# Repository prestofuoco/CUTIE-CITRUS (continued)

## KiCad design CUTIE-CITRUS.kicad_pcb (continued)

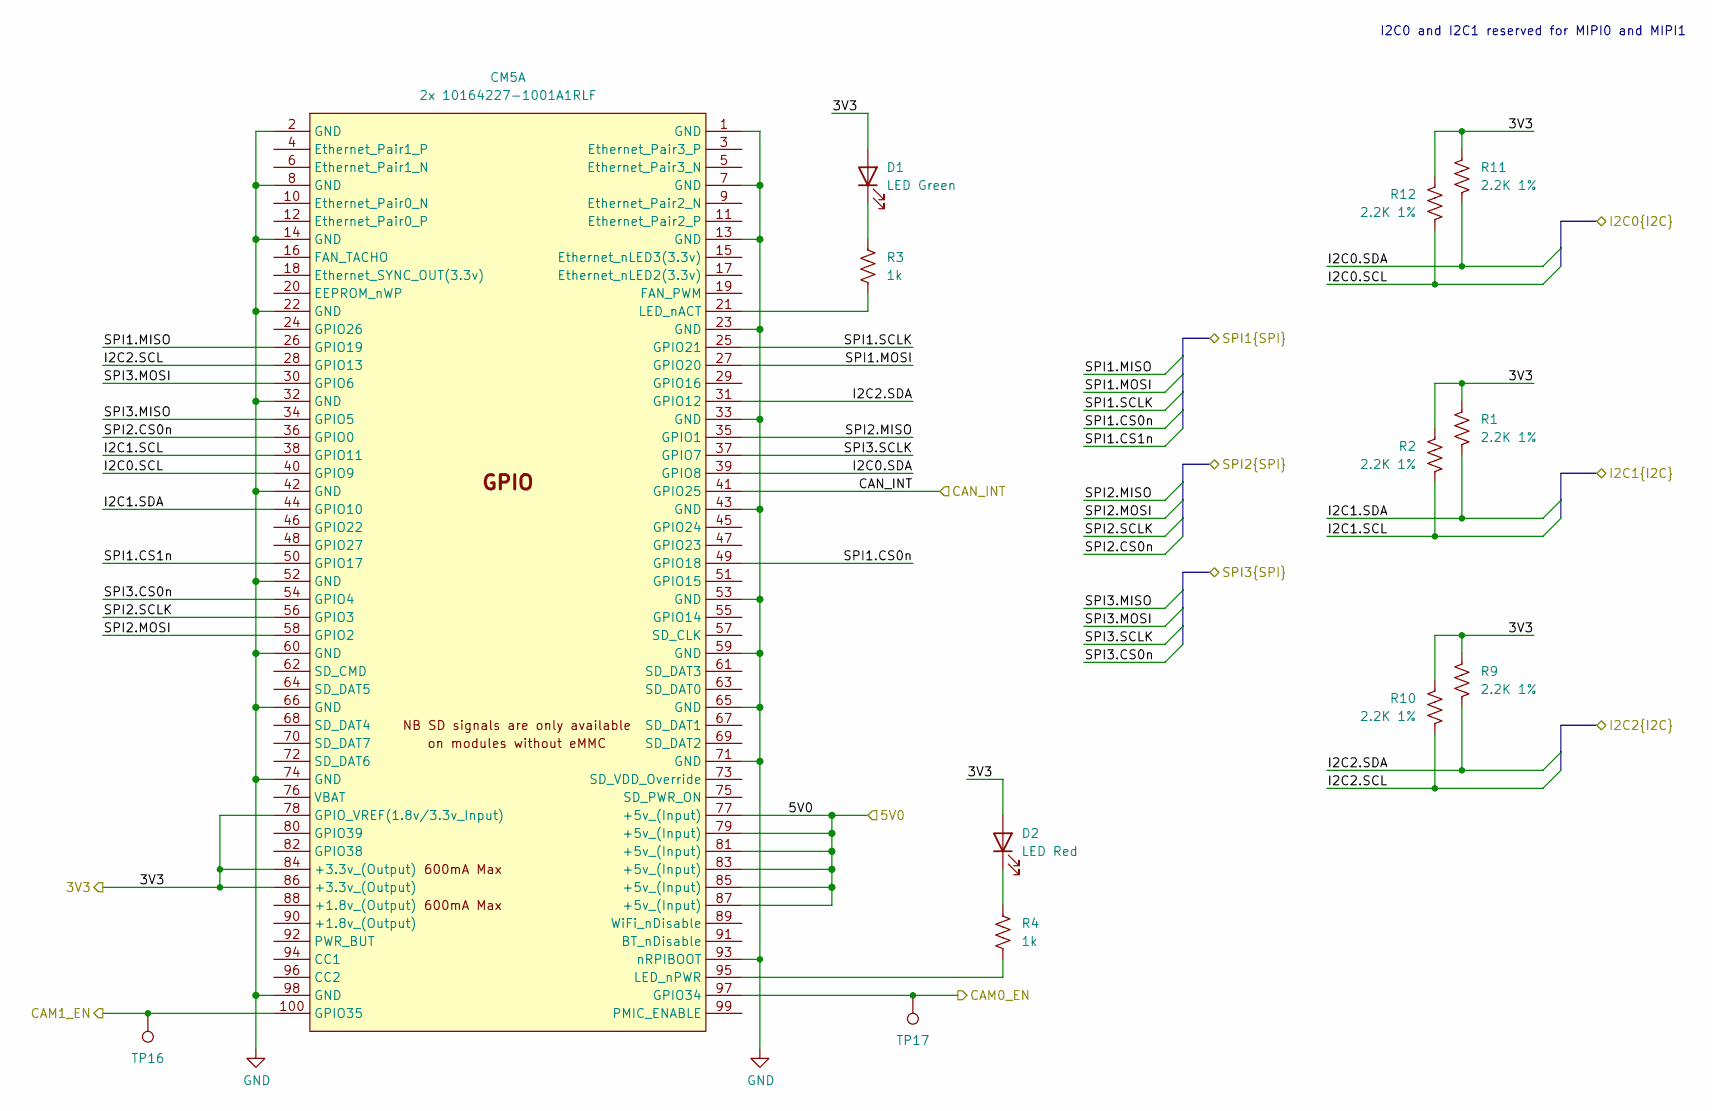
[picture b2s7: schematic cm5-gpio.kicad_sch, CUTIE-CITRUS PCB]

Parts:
CM5: 2x 10164227-1001A1RLF; RPi-CM5
D1: LED Green; LED_0603_1608Metric
D2: LED Red; LED_0603_1608Metric
R1, R2, R9, R10, R11, R12: 2.2K 1%; R_0402_1005Metric
R3, R4: 1k; R_0402_1005Metric
TP16, TP17: TestPoint; TestPoint_Pad_D1.0mm

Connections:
/Backplane Connector/5V0: CM5.77 (+5v_(Input)), CM5.79 (+5v_(Input)), CM5.81 (+5v_(Input)), CM5.83 (+5v_(Input)), CM5.85 (+5v_(Input)), CM5.87 (+5v_(Input)); also elsewhere on the board
/Backplane Connector/SPI2.CS0n: CM5.36 (GPIO0); also elsewhere on the board
/Backplane Connector/SPI2.MISO: CM5.35 (GPIO1); also elsewhere on the board
/Backplane Connector/SPI2.MOSI: CM5.58 (GPIO2); also elsewhere on the board
/Backplane Connector/SPI2.SCLK: CM5.56 (GPIO3); also elsewhere on the board
/CM5/3V3: CM5.78 (GPIO_VREF(1.8v/3.3v_Input)), CM5.84 (+3.3v_(Output)), CM5.86 (+3.3v_(Output)), D1.2 (A), D2.2 (A), R1.1, R2.1, R9.1, R10.1, R11.1, R12.1; also elsewhere on the board
/CM5/CAM0_EN: CM5.97 (GPIO34), TP17.1; also elsewhere on the board
/CM5/CAM1_EN: CM5.100 (GPIO35), TP16.1; also elsewhere on the board
/CM5/CAN_INT: CM5.41 (GPIO25); also elsewhere on the board
/CM5/GPIO/SPI3.CS0n: CM5.54 (GPIO4); also elsewhere on the board
/CM5/GPIO/SPI3.MISO: CM5.34 (GPIO5); also elsewhere on the board
/CM5/GPIO/SPI3.MOSI: CM5.30 (GPIO6); also elsewhere on the board
/CM5/GPIO/SPI3.SCLK: CM5.37 (GPIO7); also elsewhere on the board
/CM5/I2C0.SCL: CM5.40 (GPIO9), R12.2; also elsewhere on the board
/CM5/I2C0.SDA: CM5.39 (GPIO8), R11.2; also elsewhere on the board
/CM5/I2C1.SCL: CM5.38 (GPIO11), R2.2; also elsewhere on the board
/CM5/I2C1.SDA: CM5.44 (GPIO10), R1.2; also elsewhere on the board
/CM5/I2C2.SCL: CM5.28 (GPIO13), R10.2; also elsewhere on the board
/CM5/I2C2.SDA: CM5.31 (GPIO12), R9.2; also elsewhere on the board
/CM5/SPI1.CS0n: CM5.49 (GPIO18); also elsewhere on the board
/CM5/SPI1.CS1n: CM5.50 (GPIO17)
/CM5/SPI1.MISO: CM5.26 (GPIO19); also elsewhere on the board
/CM5/SPI1.MOSI: CM5.27 (GPIO20); also elsewhere on the board
/CM5/SPI1.SCLK: CM5.25 (GPIO21); also elsewhere on the board
GND: CM5.1 (GND), CM5.2 (GND), CM5.7 (GND), CM5.8 (GND), CM5.13 (GND), CM5.14 (GND), CM5.22 (GND), CM5.23 (GND), CM5.32 (GND), CM5.33 (GND), CM5.42 (GND), CM5.43 (GND), CM5.52 (GND), CM5.53 (GND), CM5.59 (GND), CM5.60 (GND), CM5.65 (GND), CM5.66 (GND), CM5.71 (GND), CM5.74 (GND), CM5.93 (nRPIBOOT), CM5.98 (GND); also elsewhere on the board
unnamed: CM5.21 (LED_nACT), R3.2
unnamed: CM5.95 (LED_nPWR), R4.2
unnamed: D1.1 (K), R3.1
unnamed: D2.1 (K), R4.1

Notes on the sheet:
I2C0 and I2C1 reserved for MIPI0 and MIPI1

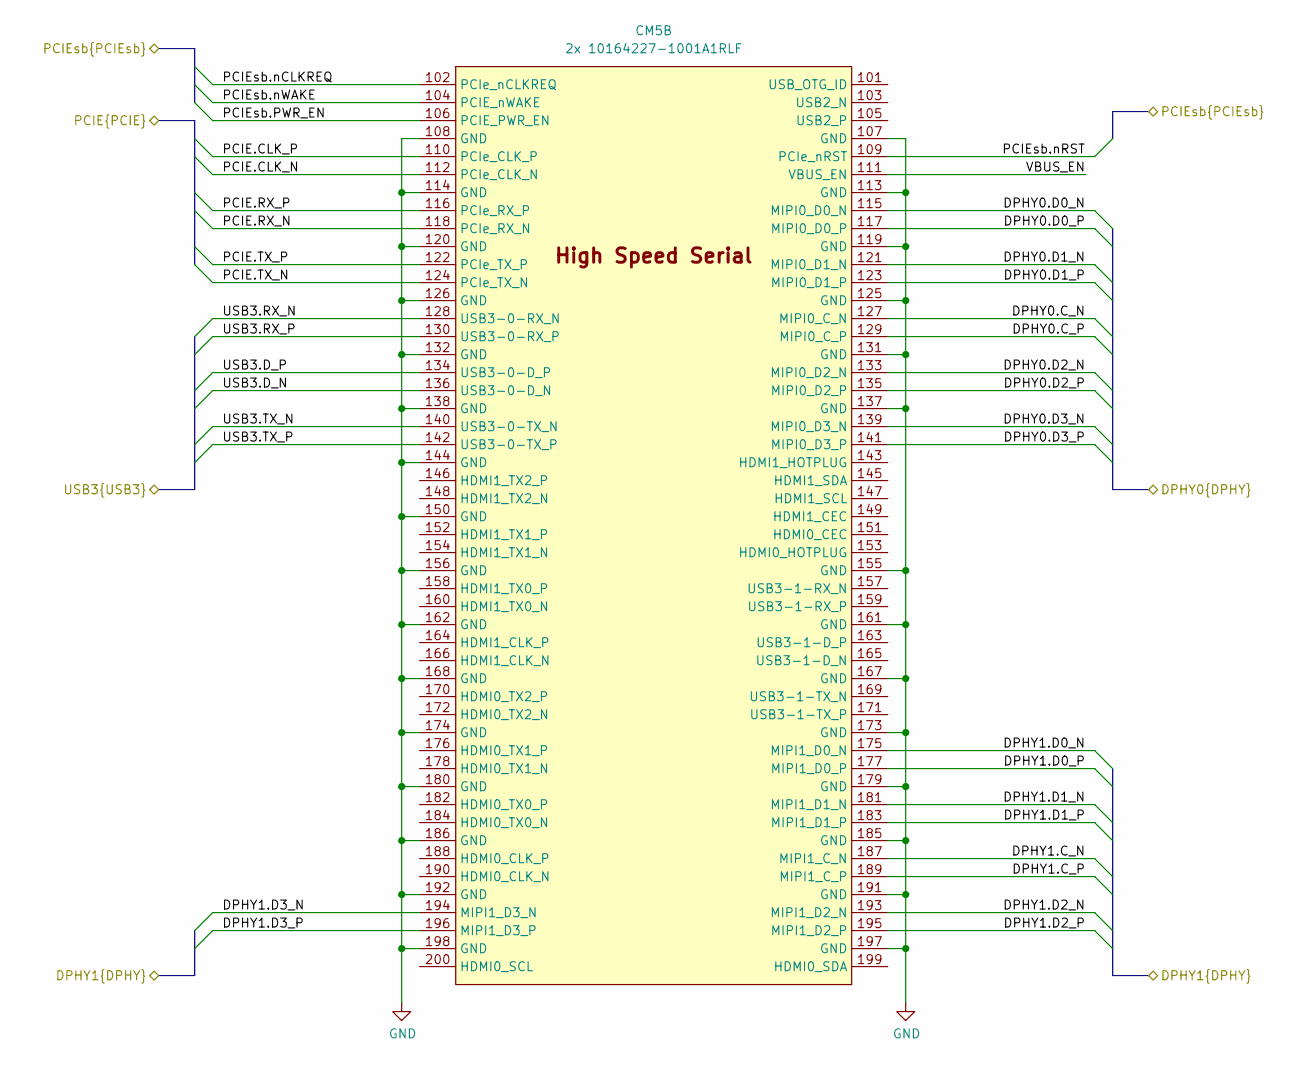
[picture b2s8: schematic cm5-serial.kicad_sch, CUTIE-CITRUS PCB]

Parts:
CM5: 2x 10164227-1001A1RLF; RPi-CM5

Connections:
/Backplane Connector/USB3.D_N: CM5.136 (USB3-0-D_N); also elsewhere on the board
/Backplane Connector/USB3.D_P: CM5.134 (USB3-0-D_P); also elsewhere on the board
/Backplane Connector/USB3.RX_N: CM5.128 (USB3-0-RX_N); also elsewhere on the board
/Backplane Connector/USB3.RX_P: CM5.130 (USB3-0-RX_P); also elsewhere on the board
/Backplane Connector/USB3.TX_N: CM5.140 (USB3-0-TX_N); also elsewhere on the board
/Backplane Connector/USB3.TX_P: CM5.142 (USB3-0-TX_P); also elsewhere on the board
/CM5/DPHY0.C_N: CM5.127 (MIPI0_C_N); also elsewhere on the board
/CM5/DPHY0.C_P: CM5.129 (MIPI0_C_P); also elsewhere on the board
/CM5/DPHY0.D0_N: CM5.115 (MIPI0_D0_N); also elsewhere on the board
/CM5/DPHY0.D0_P: CM5.117 (MIPI0_D0_P); also elsewhere on the board
/CM5/DPHY0.D1_N: CM5.121 (MIPI0_D1_N); also elsewhere on the board
/CM5/DPHY0.D1_P: CM5.123 (MIPI0_D1_P); also elsewhere on the board
/CM5/DPHY0.D2_N: CM5.133 (MIPI0_D2_N); also elsewhere on the board
/CM5/DPHY0.D2_P: CM5.135 (MIPI0_D2_P); also elsewhere on the board
/CM5/DPHY0.D3_N: CM5.139 (MIPI0_D3_N); also elsewhere on the board
/CM5/DPHY0.D3_P: CM5.141 (MIPI0_D3_P); also elsewhere on the board
/CM5/DPHY1.C_N: CM5.187 (MIPI1_C_N); also elsewhere on the board
/CM5/DPHY1.C_P: CM5.189 (MIPI1_C_P); also elsewhere on the board
/CM5/DPHY1.D0_N: CM5.175 (MIPI1_D0_N); also elsewhere on the board
/CM5/DPHY1.D0_P: CM5.177 (MIPI1_D0_P); also elsewhere on the board
/CM5/DPHY1.D1_N: CM5.181 (MIPI1_D1_N); also elsewhere on the board
/CM5/DPHY1.D1_P: CM5.183 (MIPI1_D1_P); also elsewhere on the board
/CM5/DPHY1.D2_N: CM5.193 (MIPI1_D2_N); also elsewhere on the board
/CM5/DPHY1.D2_P: CM5.195 (MIPI1_D2_P); also elsewhere on the board
/CM5/DPHY1.D3_N: CM5.194 (MIPI1_D3_N); also elsewhere on the board
/CM5/DPHY1.D3_P: CM5.196 (MIPI1_D3_P); also elsewhere on the board
/CM5/High-Speed Serial/VBUS_EN: CM5.111 (VBUS_EN)
/CM5/PCIE.CLK_N: CM5.112 (PCIe_CLK_N); also elsewhere on the board
/CM5/PCIE.CLK_P: CM5.110 (PCIe_CLK_P); also elsewhere on the board
/CM5/PCIE.RX_N: CM5.118 (PCIe_RX_N); also elsewhere on the board
/CM5/PCIE.RX_P: CM5.116 (PCIe_RX_P); also elsewhere on the board
/CM5/PCIE.TX_N: CM5.124 (PCIe_TX_N); also elsewhere on the board
/CM5/PCIE.TX_P: CM5.122 (PCIe_TX_P); also elsewhere on the board
/CM5/PCIEsb.PWR_EN: CM5.106 (PCIE_PWR_EN); also elsewhere on the board
/CM5/PCIEsb.nCLKREQ: CM5.102 (PCIe_nCLKREQ); also elsewhere on the board
/CM5/PCIEsb.nRST: CM5.109 (PCIe_nRST); also elsewhere on the board
/CM5/PCIEsb.nWAKE: CM5.104 (PCIE_nWAKE); also elsewhere on the board
GND: CM5.107 (GND), CM5.108 (GND), CM5.113 (GND), CM5.114 (GND), CM5.119 (GND), CM5.120 (GND), CM5.125 (GND), CM5.126 (GND), CM5.131 (GND), CM5.132 (GND), CM5.137 (GND), CM5.138 (GND), CM5.144 (GND), CM5.150 (GND), CM5.155 (GND), CM5.156 (GND), CM5.161 (GND), CM5.162 (GND), CM5.167 (GND), CM5.168 (GND), CM5.173 (GND), CM5.174 (GND), CM5.179 (GND), CM5.180 (GND), CM5.185 (GND), CM5.186 (GND), CM5.191 (GND), CM5.192 (GND), CM5.197 (GND), CM5.198 (GND); also elsewhere on the board

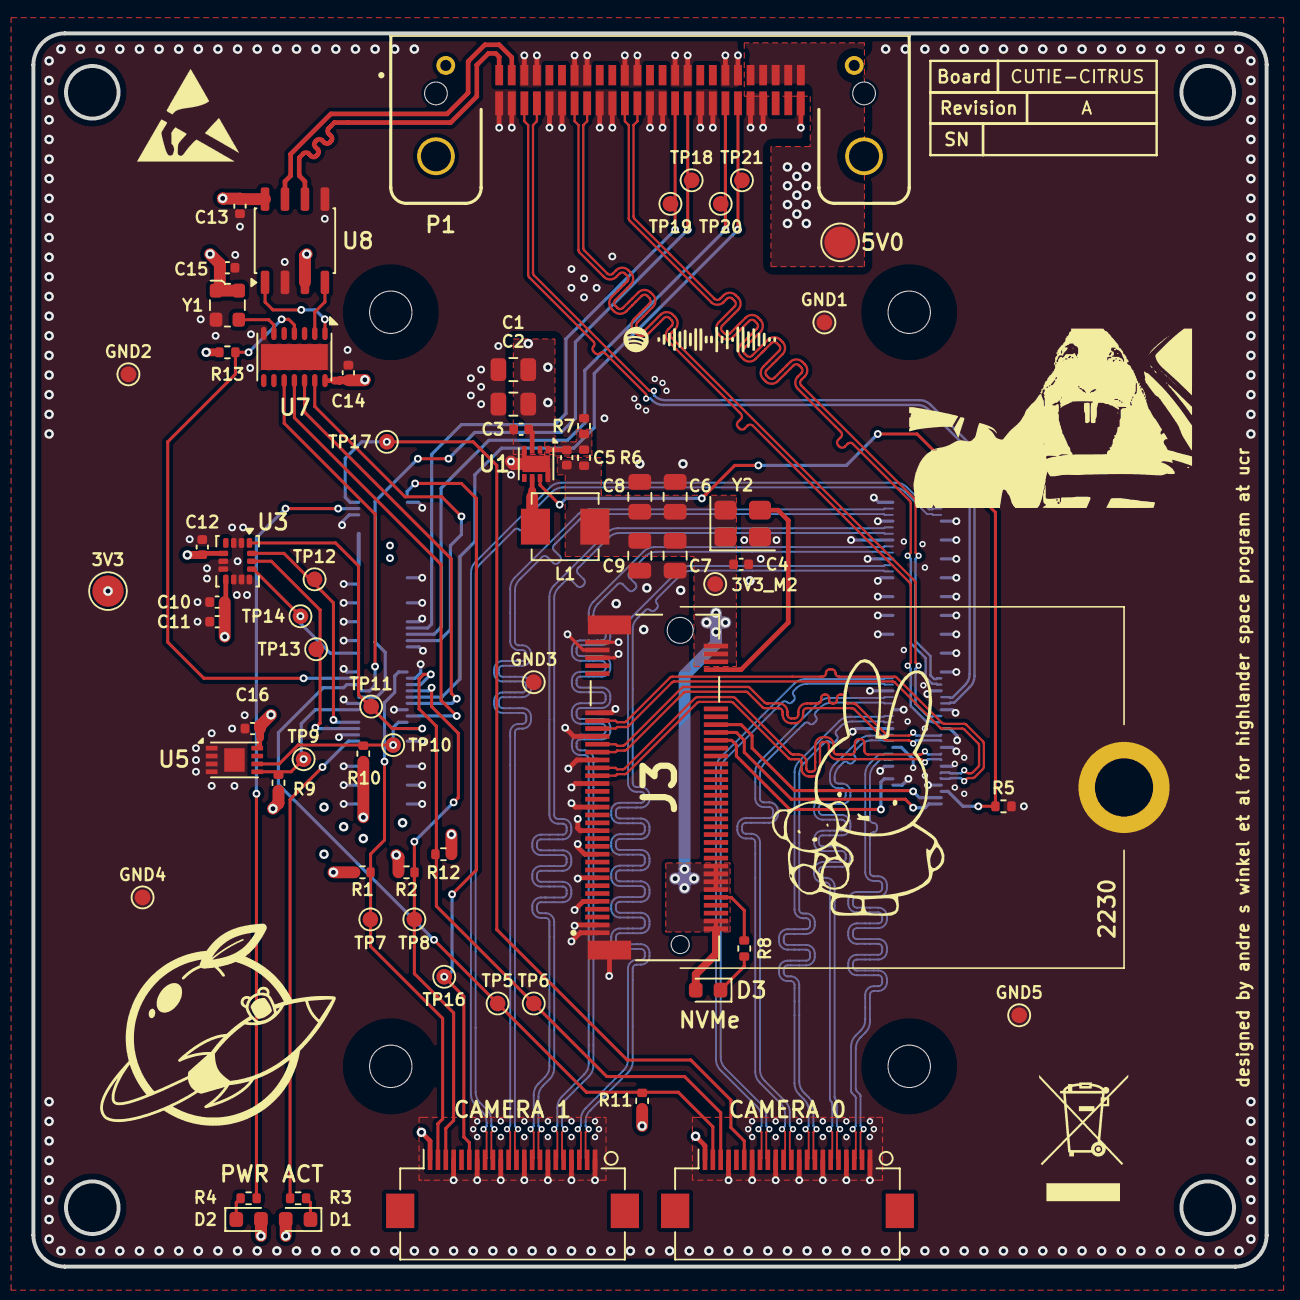
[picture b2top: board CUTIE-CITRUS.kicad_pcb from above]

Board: 4 copper layers, 78.5 x 78.5 mm, 69 parts (1 on the bottom side), 75 nets.

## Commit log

2025-10-11 added gitignore and gitattributes
2025-10-11 initial commit for kicad
2025-10-11 restructured
2025-10-11 add project title to readme
2025-10-18 added misc
2025-11-03 saved libs to project, initialized hierarchy
2025-11-11 added fpc connector
2025-11-15 quick push
2025-11-16 added m2 mkey conn, defined signals
2025-11-17 restructured symbols, added footprints
2025-11-20 quick push, no major change
2025-11-23 added second camera, 6-axis imu
2025-11-24 annotations, small fixes
2025-11-25 extra abstraction layer for cm5 conns.
2025-11-25 add top-level sch img to readme
2025-11-28 abstractified pcie sideband sigs
2025-11-28 updated top-level schematic image
2025-12-11 neo m8m impl.
2025-12-12 prepared usb3, abstracted cameras, backplane connector
2025-12-12 un-abstraction, footprints, layout edge cuts
2025-12-12 moved TPs
2025-12-12 moved power TPs to cm5 sheet
2025-12-12 added pdf
2025-12-13 added temp sensors
2025-12-13 corrected temp sens i2c addr
2025-12-15 added potential backplane conn
2025-12-16 added conns to backplane
2025-12-19 removed ublox
2025-12-19 defined can
2025-12-22 finished defining spi/i2c gpio, CAN, off-board signals
2025-12-23 starting layout
2025-12-24 high-speed signals initial
2025-12-24 3v3_m2 and 5v0 power planes
2025-12-24 add pcb view to readme
2025-12-26 power planes and sensor placement
2025-12-26 preliminary layout complete
2025-12-27 silkscreen edits
2025-12-27 drc fixes, verification
2025-12-27 Add additional images to README
2025-12-27 added missing 3d files, added slksc graphics
2025-12-29 silkscreen, via stitching
2025-12-29 tp and gnd vias fixes
2025-12-29 updated images
2025-12-29 redid gpio layout, removed one temp sensor, bom
2025-12-29 add layout pdf
2025-12-29 Update README with document references
    Added references to CUTIE-CITRUS.pdf and layout.pdf for additional documentation.
2026-01-15 added fabrication outputs, replaced imu drop-in og imu was out of stock everywhere, invensense drop-in replacement
2026-01-16 fixes for fab
2026-01-16 restructure for embedded
2026-01-16 edited gitignore for src
2026-01-17 initial commit for citrus v2
2026-01-17 initial pcb commit for v2
2026-01-19 added xc7z020clg484 symbol and hierarchy
2026-01-20 hierarchy and cleaning
2026-01-21 schematic structure, added qspi flash, pinout defs. mostly work on PS pinouts, defining comms. buses, still need to choose dram part, phys, camera/bus, power supply etc
2026-01-21 edits to eth0 protocol names / bus aliases
2026-01-22 added ddr3l
2026-01-22 add eth phy
2026-01-22 phy and debug ffc conn
2026-01-24 nightly build
2026-01-24 add ci/cd workflow
2026-01-24 try again with different flags
2026-01-25 try again, removed include vias
2026-01-25 read the docs, finally
2026-01-25 fixed for case sensitivity
2026-01-25 final fix ci/cd
2026-01-25 fab outputs
2026-01-25 more pin definition pending define for how boot mode and power cycling will work, potential uc (stm32)
2026-01-26 fices for boot definition
2026-01-26 byte swapping and rough layout
2026-01-27 power
